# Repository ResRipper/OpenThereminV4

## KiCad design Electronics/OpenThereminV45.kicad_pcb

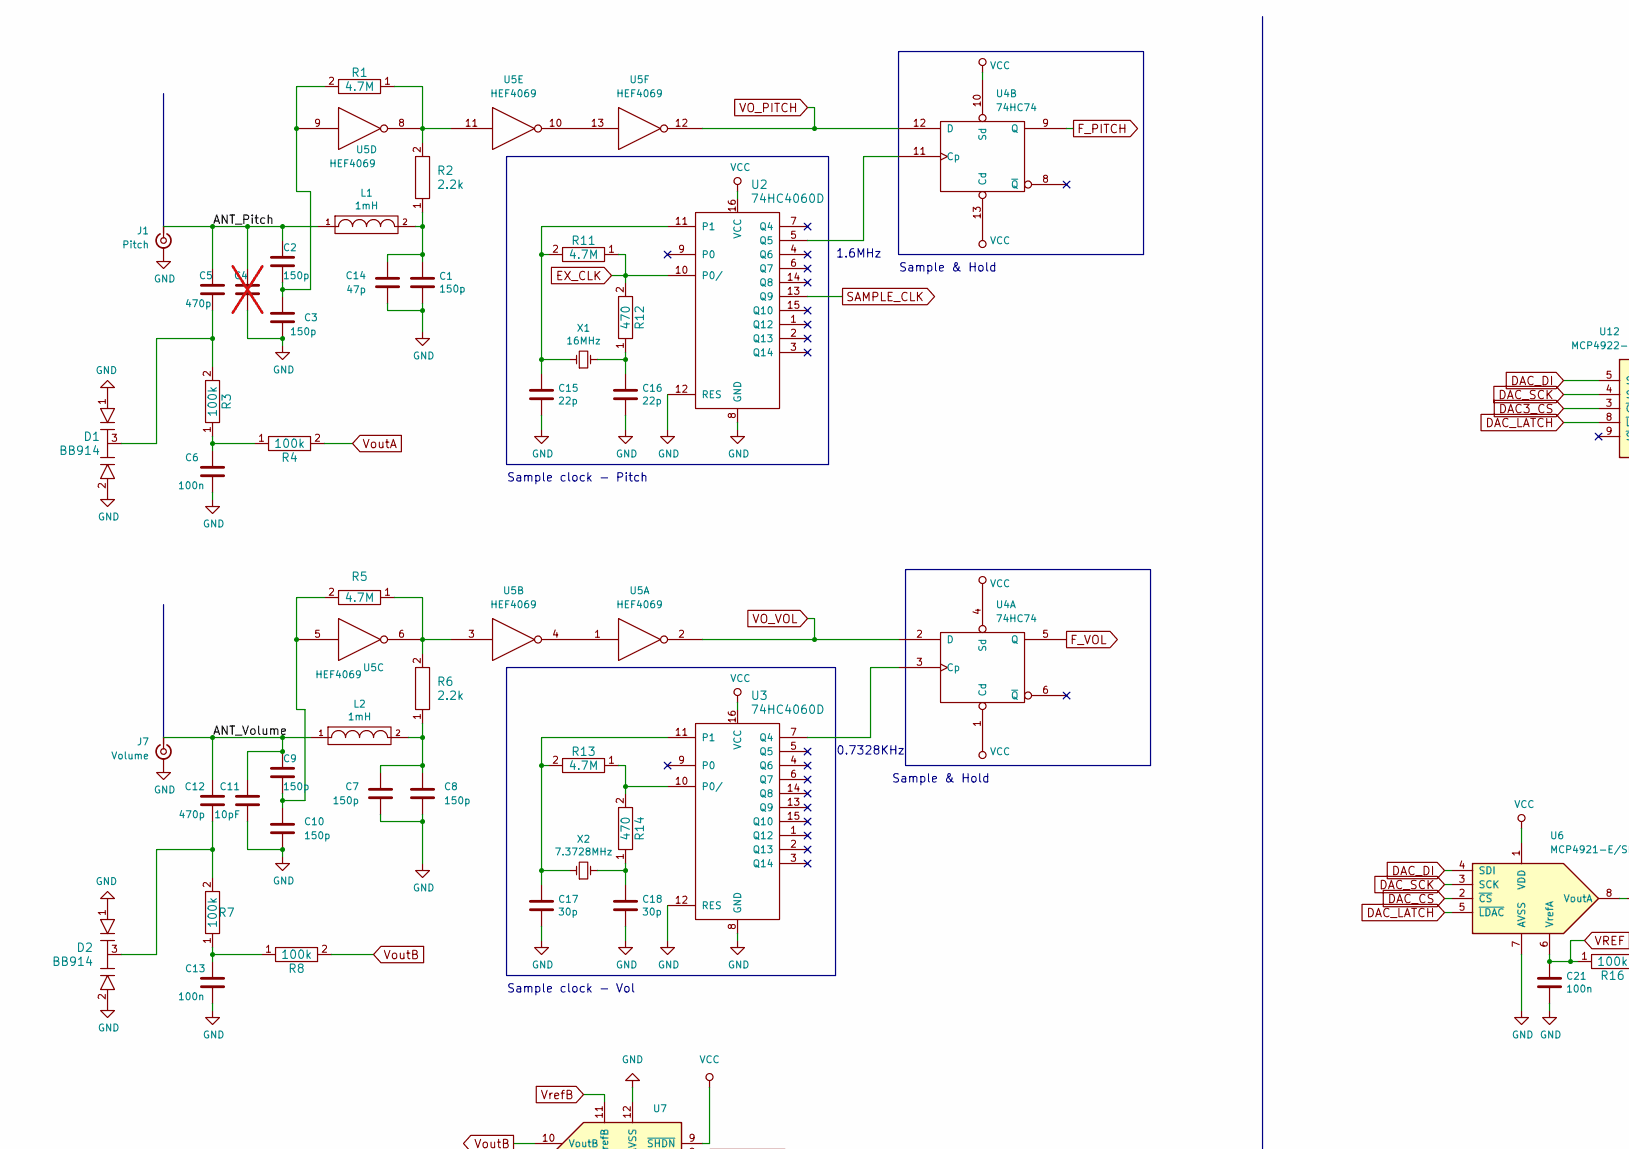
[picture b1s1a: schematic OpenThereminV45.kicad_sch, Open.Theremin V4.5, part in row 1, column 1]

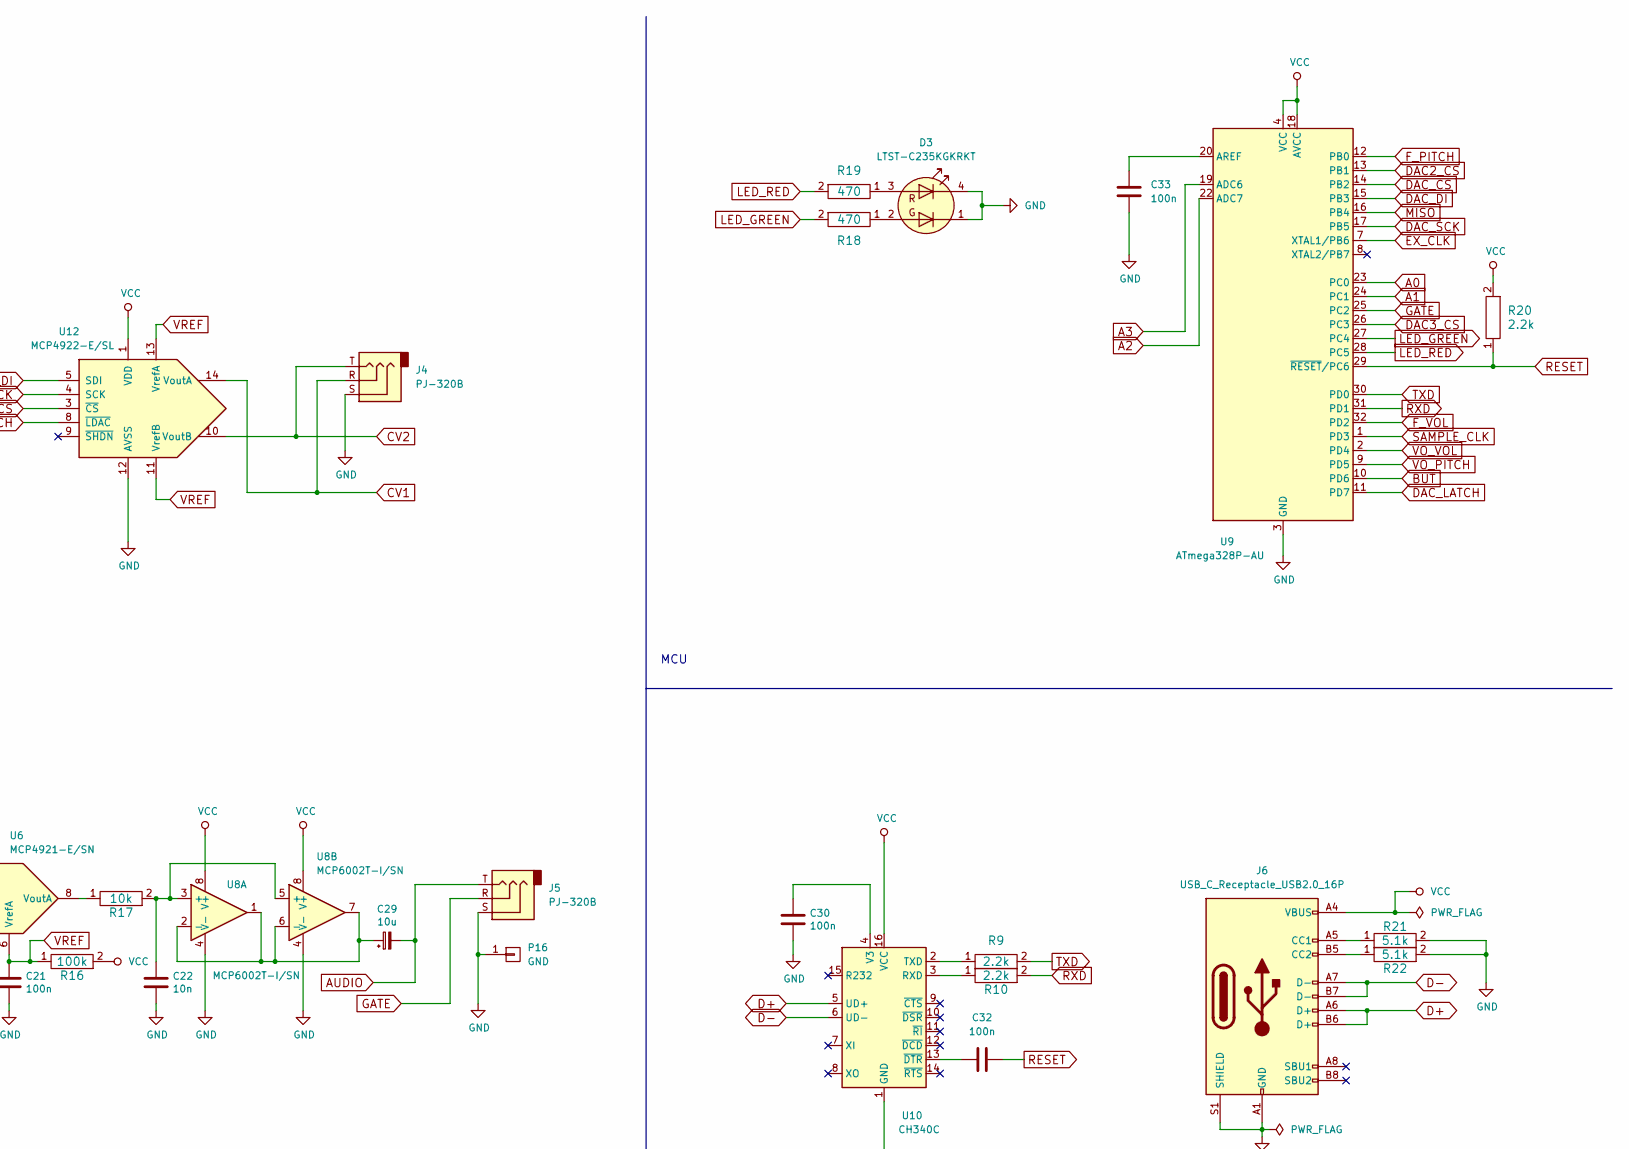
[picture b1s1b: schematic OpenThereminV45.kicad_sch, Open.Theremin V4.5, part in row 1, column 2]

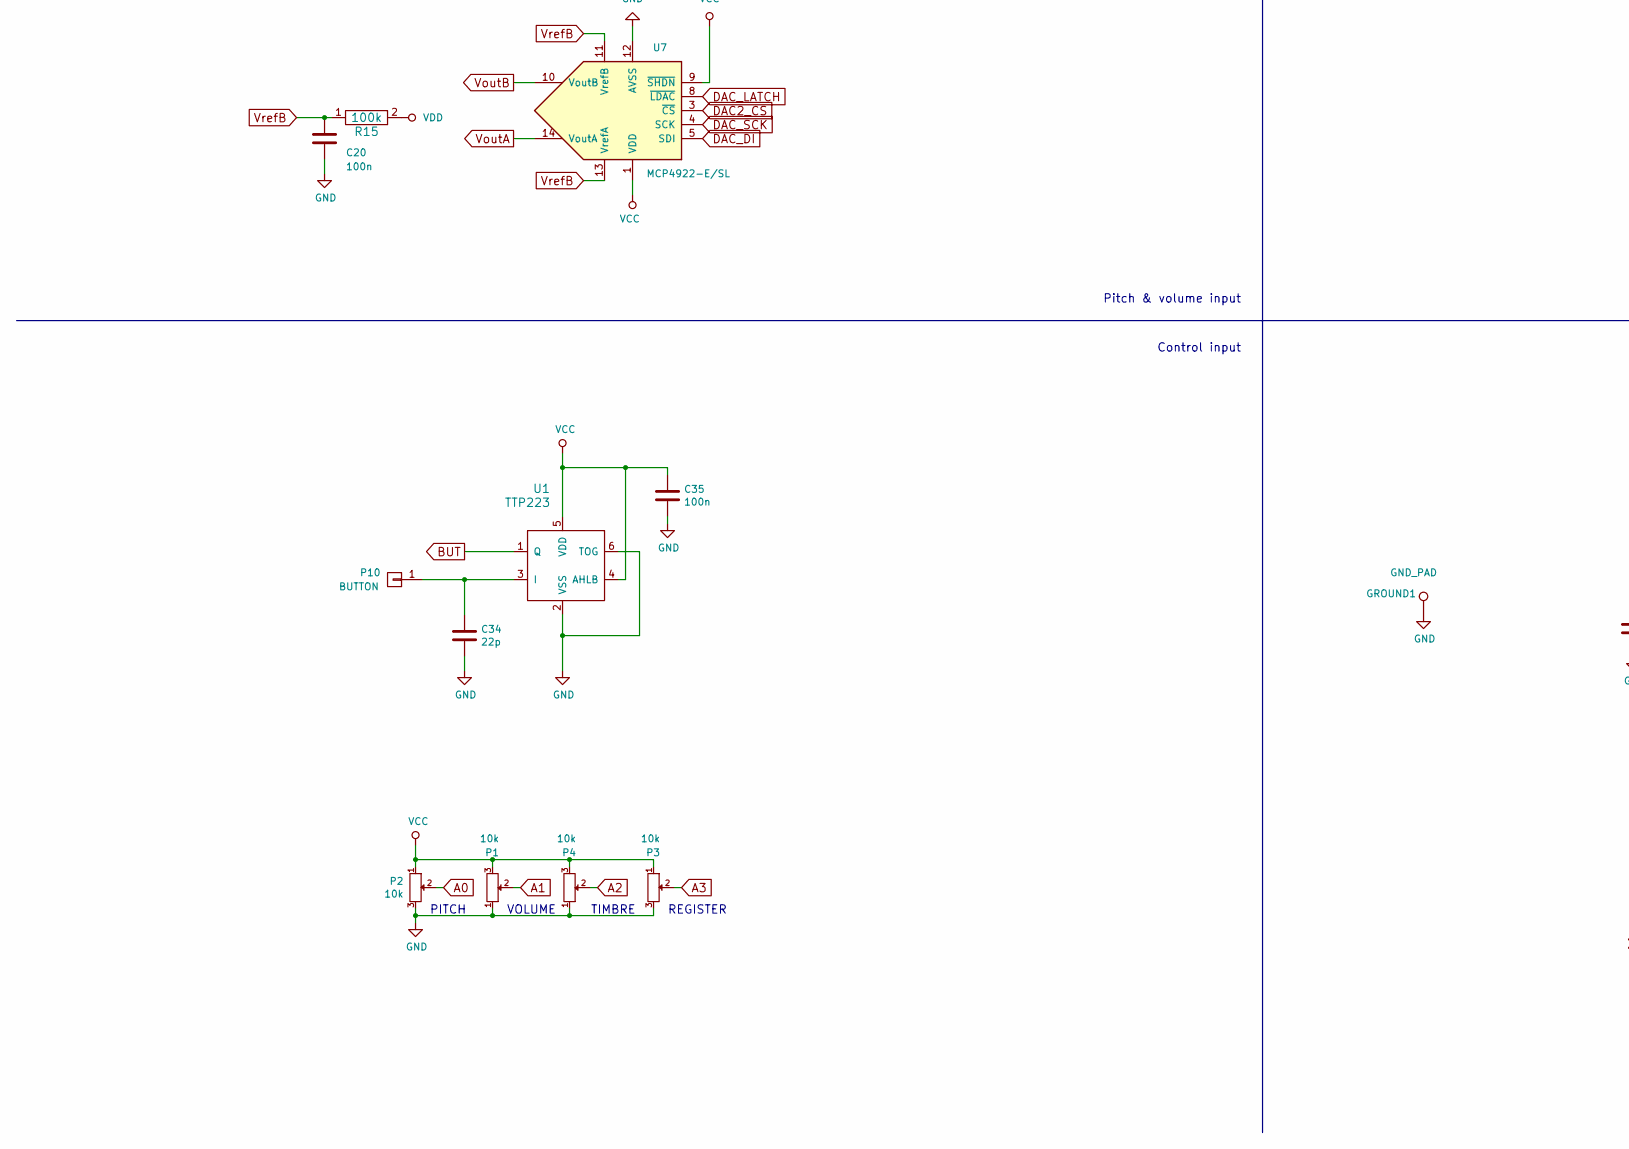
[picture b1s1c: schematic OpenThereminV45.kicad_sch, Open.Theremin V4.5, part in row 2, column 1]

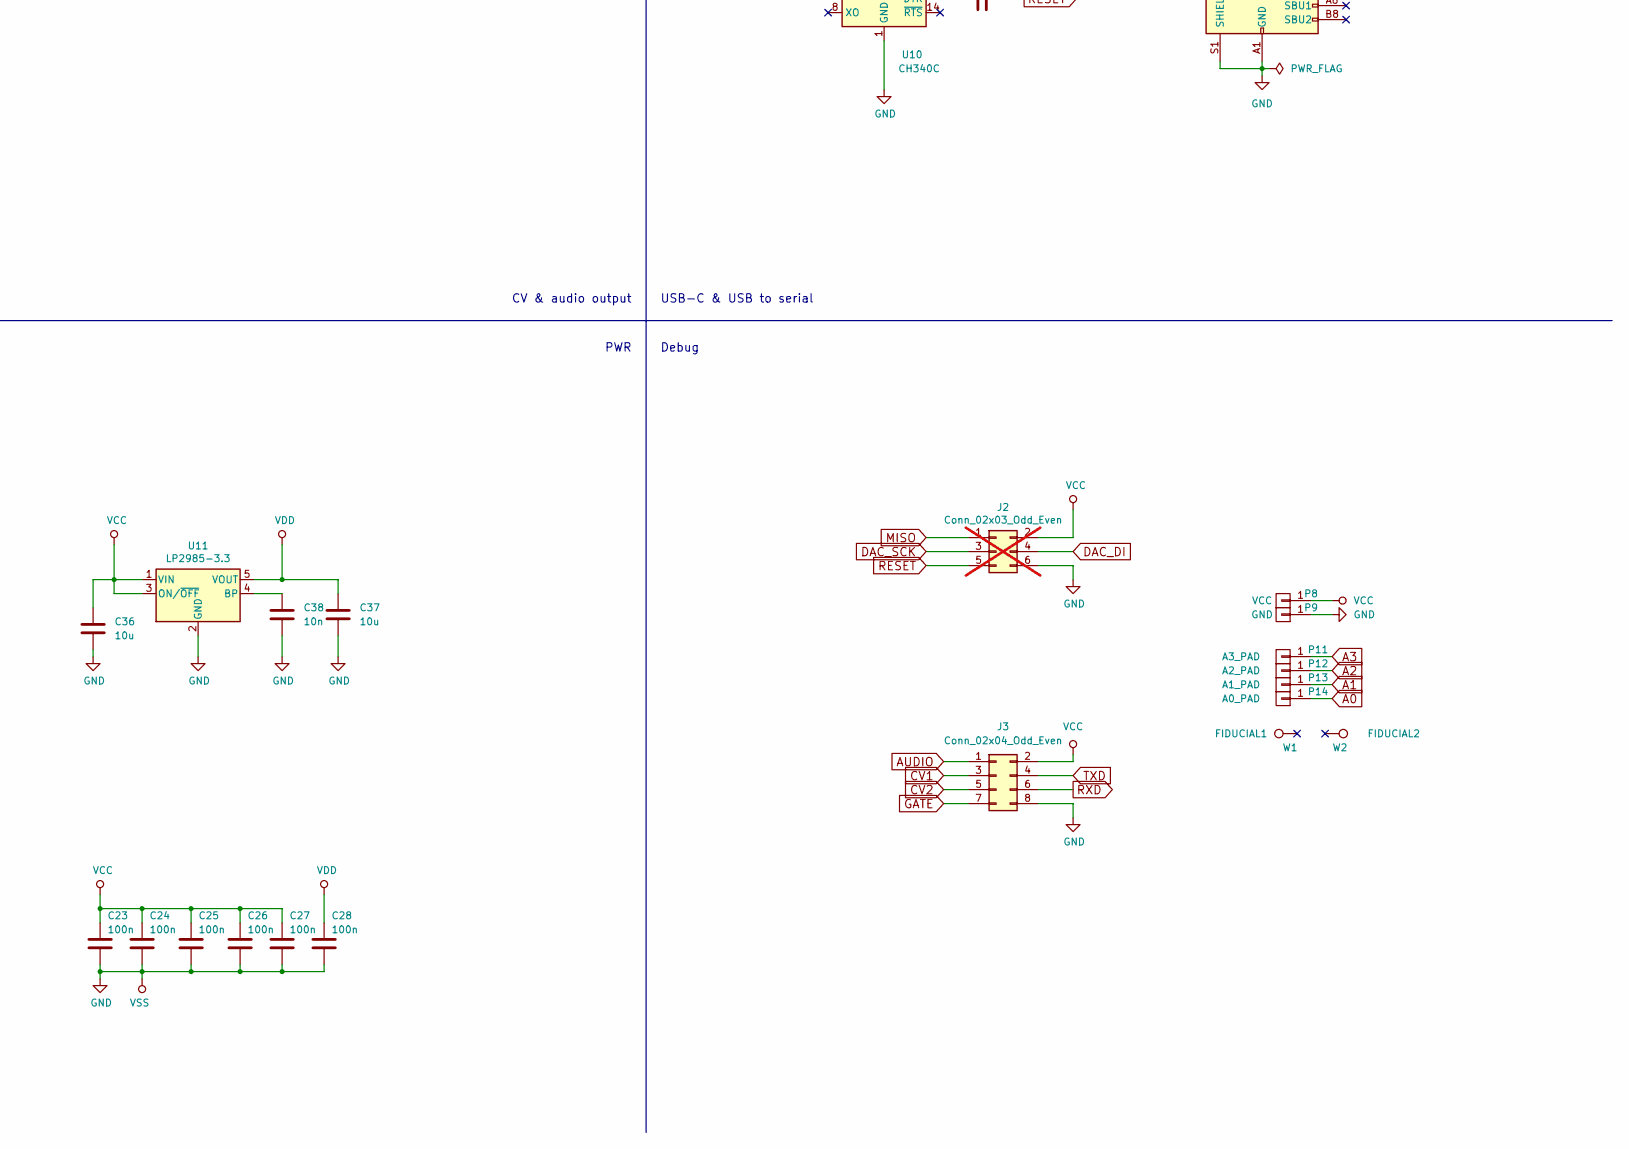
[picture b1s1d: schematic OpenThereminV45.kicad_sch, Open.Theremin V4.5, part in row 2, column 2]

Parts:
C1, C2, C3, C7, C8, C9, C10: 150p; C_0603_1608Metric; LCSC C107038
C4: C_0603_1608Metric; not fitted
C5, C12: 470p; C_0603_1608Metric; LCSC C106211
C6, C13, C20, C21, C23, C24, C25, C26, C27, C28, C30, C32, C33, C35: 100n; C_0603_1608Metric; LCSC C282519
C11: 10pF; C_0603_1608Metric; LCSC C376764
C14: 47p; C_0603_1608Metric; LCSC C94904
C15, C16, C34: 22p; C_0603_1608Metric; LCSC C105620
C17, C18: 30p; C_0603_1608Metric; LCSC C107047
C22, C38: 10n; C_0603_1608Metric; LCSC C376807
C29, C36, C37: 10u; C_0603_1608Metric; LCSC C1691
D1, D2: BB914; SOT-23; LCSC C3272485
D3: LTST-C235KGKRKT; LED_LiteOn_LTST-C235KGKRKT; LCSC C125110
GROUND1: GND_PAD; GNDPad
J1: Pitch; SMA_Amphenol_132134-11_Vertical; LCSC C5723187
J2: Conn_02x03_Odd_Even; Tag-Connect_TC2030-IDC-NL_2x03_P1.27mm_Vertical; not fitted
J3: Conn_02x04_Odd_Even; PinHeader_2x04_P1.27mm_Vertical_SMD; LCSC C19268845
J4, J5: PJ-320B; XKB_PJ-320B; LCSC C2884998
J6: USB_C_Receptacle_USB2.0_16P; USB_C_Receptacle_GCT_USB4105-xx-A_16P_TopMnt_Horizontal; LCSC C2988369
J7: Volume; SMA_Amphenol_132134-11_Vertical; LCSC C5723187
L1, L2: 1mH; L_1812_4532Metric; LCSC C394145
P1, P2, P3, P4: 10k; ALPS_RK09K1130A6S; LCSC C209770
P8: VCC; SMD_Pinheader_1_OT_BLANK
P9, P16: GND; SMD_Pinheader_1_OT_BLANK
P10: BUTTON; SensorButton
P11: A3_PAD; SMD_Pinheader_1_OT_BLANK
P12: A2_PAD; SMD_Pinheader_1_OT_BLANK
P13: A1_PAD; SMD_Pinheader_1_OT_BLANK
P14: A0_PAD; SMD_Pinheader_1_OT_BLANK
R1, R5, R11, R13: 4.7M; R_0603_1608Metric; LCSC C322165
R2, R6, R9, R10, R20: 2.2k; R_0603_1608Metric; LCSC C294652
R3, R4, R7, R8, R15, R16: 100k; R_0603_1608Metric; LCSC C3152121
R12, R14, R18, R19: 470; R_0603_1608Metric; LCSC C116694
R17: 10k; R_0603_1608Metric; LCSC C3152123
R21, R22: 5.1k; R_0603_1608Metric; LCSC C3152148
U1: TTP223; SOT-23-6; LCSC C5345654
U2, U3: 74HC4060D; SOIC-16_3.9x9.9mm_P1.27mm; LCSC C5649
U4: 74HC74; SOIC-14_3.9x8.7mm_P1.27mm; LCSC C27597
U5: HEF4069; SOIC-14_3.9x8.7mm_P1.27mm; LCSC C6739
U6: MCP4921-E/SN; SOIC-8_3.9x4.9mm_P1.27mm; LCSC C43499
U7, U12: MCP4922-E/SL; SOIC-14_3.9x8.7mm_P1.27mm; LCSC C39851
U8: MCP6002T-I/SN; SOIC-8_3.9x4.9mm_P1.27mm; LCSC C20538868
U9: ATmega328P-AU; TQFP-32_7x7mm_P0.8mm; LCSC C14877
U10: CH340C; SOIC-16_3.9x9.9mm_P1.27mm; LCSC C84681
U11: LP2985-3.3; SOT-23-5; LCSC C95414
W1: FIDUCIAL1; Fiducial_1mm_Dia_2.54mm_Outer_CopperBottom
W2: FIDUCIAL2; Fiducial_1mm_Dia_2.54mm_Outer_CopperBottom
X1: 16MHz; Crystal_SMD_HC49-SD; LCSC C7473031
X2: 7.3728MHz; Crystal_SMD_HC49-SD; LCSC C19173022

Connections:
/ANT_Pitch: C2.1, C4.1, C5.1, J1.1 (In), L1.1
/ANT_Volume: C9.1, C11.1, C12.1, J7.1 (In), L2.1
A0: P2.2, P14.1, U9.23 (PC0)
A1: P1.2, P13.1, U9.24 (PC1)
A2: P4.2, P12.1, U9.22 (ADC7)
A3: P3.2, P11.1, U9.19 (ADC6)
AUDIO: C29.2, J3.1, J5.T
BUT: U1.1 (Q), U9.10 (PD6)
CV1: J3.3, J4.R, U12.14 (VoutA)
CV2: J3.5, J4.T, U12.10 (VoutB)
D+: J6.A6 (D+), J6.B6 (D+), U10.5 (UD+)
D-: J6.A7 (D-), J6.B7 (D-), U10.6 (UD-)
DAC2_CS: U7.3 (~CS), U9.13 (PB1)
DAC3_CS: U9.26 (PC3), U12.3 (~CS)
DAC_CS: U6.2 (~CS), U9.14 (PB2)
DAC_DI: J2.4, U6.4 (SDI), U7.5 (SDI), U9.15 (PB3), U12.5 (SDI)
DAC_LATCH: U6.5 (~LDAC), U7.8 (~LDAC), U9.11 (PD7), U12.8 (~LDAC)
DAC_SCK: J2.3, U6.3 (SCK), U7.4 (SCK), U9.17 (PB5), U12.4 (SCK)
EX_CLK: R11.1, R12.2, U2.10 (P0/), U9.7 (XTAL1/PB6)
F_PITCH: U4.9 (Q), U9.12 (PB0)
F_VOL: U4.5 (Q), U9.32 (PD2)
GATE: J3.7, J5.R, U9.25 (PC2)
GND: C1.2, C3.2, C4.2, C6.2, C7.2, C8.2, C10.2, C11.2, C13.2, C14.2, C15.2, C16.2, C17.2, C18.2, C20.2, C21.2, C22.2, C23.2, C24.2, C25.2, C26.2, C27.2, C28.2, C30.2, C33.2, C34.2, C35.2, C36.2, C37.2, C38.2, D1.1, D1.2, D2.1, D2.2, D3.1 (K2), D3.4 (K1), GROUND1.1, J1.2 (Ext), J2.6, J3.8, J4.S, J5.S, J6.A1 (GND), J6.A12 (GND), J6.B1 (GND), J6.B12 (GND), J6.S1 (SHIELD), J7.2 (Ext), P1.1, P2.3, P3.3, P4.1, P9.1, P16.1, R21.2, R22.2, U1.2 (VSS), U1.6 (TOG), U2.8 (GND), U2.12 (RES), U3.8 (GND), U3.12 (RES), U4.7 (GND), U5.7 (VSS), U6.7 (AVSS), U7.12 (AVSS), U8.4 (V-), U9.3 (GND), U9.5 (GND), U9.21 (GND), U10.1 (GND), U11.2 (GND), U12.12 (AVSS)
LED_GREEN: R18.2, U9.27 (PC4)
LED_RED: R19.2, U9.28 (PC5)
MISO: J2.1, U9.16 (PB4)
unnamed: C1.1, C14.1, L1.2, R2.1
unnamed: C2.2, C3.1, R1.2, U5.9
unnamed: C5.2, D1.3, R3.2
unnamed: C6.1, R3.1, R4.1
unnamed: C7.1, C8.1, L2.2, R6.1
unnamed: C9.2, C10.1, R5.2, U5.5
unnamed: C12.2, D2.3, R7.2
unnamed: C13.1, R7.1, R8.1
unnamed: C16.1, R12.1, X1.2
unnamed: C18.1, R14.1, X2.2
unnamed: D3.3 (A1), R19.1
unnamed: D3.2 (A2), R18.1
unnamed: J6.A5 (CC1), R21.1
unnamed: J6.B5 (CC2), R22.1
unnamed: C34.1, P10.1, U1.3 (I)
unnamed: R1.1, R2.2, U5.8, U5.11
unnamed: R5.1, R6.2, U5.3, U5.6
unnamed: C15.1, R11.2, U2.11 (P1), X1.1
unnamed: U2.5 (Q5), U4.11 (Cp)
unnamed: R13.1, R14.2, U3.10 (P0/)
unnamed: C17.1, R13.2, U3.11 (P1), X2.1
unnamed: U3.7 (Q4), U4.3 (Cp)
unnamed: U5.1, U5.4
unnamed: U5.10, U5.13
unnamed: R17.1, U6.8 (VoutA)
unnamed: C22.1, R17.2, U8.3 (+), U8.5 (+)
unnamed: C29.1, U8.1, U8.2 (-), U8.6 (-), U8.7
unnamed: C33.1, U9.20 (AREF)
unnamed: R10.1, U10.3 (RXD)
unnamed: R9.1, U10.2 (TXD)
unnamed: C30.1, U10.4 (V3)
unnamed: C32.2, U10.13 (~DTR)
unnamed: C38.1, U11.4 (BP)
RESET: C32.1, J2.5, R20.1, U9.29 (~RESET/PC6)
RXD: J3.6, R10.2, U9.31 (PD1)
SAMPLE_CLK: U2.13 (Q9), U9.1 (PD3)
TXD: J3.4, R9.2, U9.30 (PD0)
VCC: C23.1, C24.1, C25.1, C26.1, C27.1, C35.1, C36.1, J2.2, J3.2, J6.A4 (VBUS), J6.A9 (VBUS), J6.B4 (VBUS), J6.B9 (VBUS), P1.3, P2.1, P3.1, P4.3, P8.1, R16.2, R20.2, U1.4 (AHLB), U1.5 (VDD), U2.16 (VCC), U3.16 (VCC), U4.1 (Cd), U4.4 (Sd), U4.10 (Sd), U4.13 (Cd), U4.14 (VCC), U6.1 (VDD), U7.1 (VDD), U7.9 (~SHDN), U8.8 (V+), U9.4 (VCC), U9.6 (VCC), U9.18 (AVCC), U10.16 (VCC), U11.1 (VIN), U11.3 (ON/~OFF), U12.1 (VDD)
VDD: C28.1, C37.1, R15.2, U5.14 (VDD), U11.5 (VOUT)
VO_PITCH: U4.12 (D), U5.12, U9.9 (PD5)
VO_VOL: U4.2 (D), U5.2, U9.2 (PD4)
VREF: C21.1, R16.1, U6.6 (VrefA), U12.11 (VrefB), U12.13 (VrefA)
VoutA: R4.2, U7.14 (VoutA)
VoutB: R8.2, U7.10 (VoutB)
VrefB: C20.1, R15.1, U7.11 (VrefB), U7.13 (VrefA)

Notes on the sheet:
Sample clock - Pitch
PWR
Sample & Hold
REGISTER
MCU
0.7328KHz
VOLUME
Pitch & volume input
TIMBRE
PITCH
Debug
USB-C & USB to serial
Sample clock - Vol
1.6MHz
CV & audio output
Control input

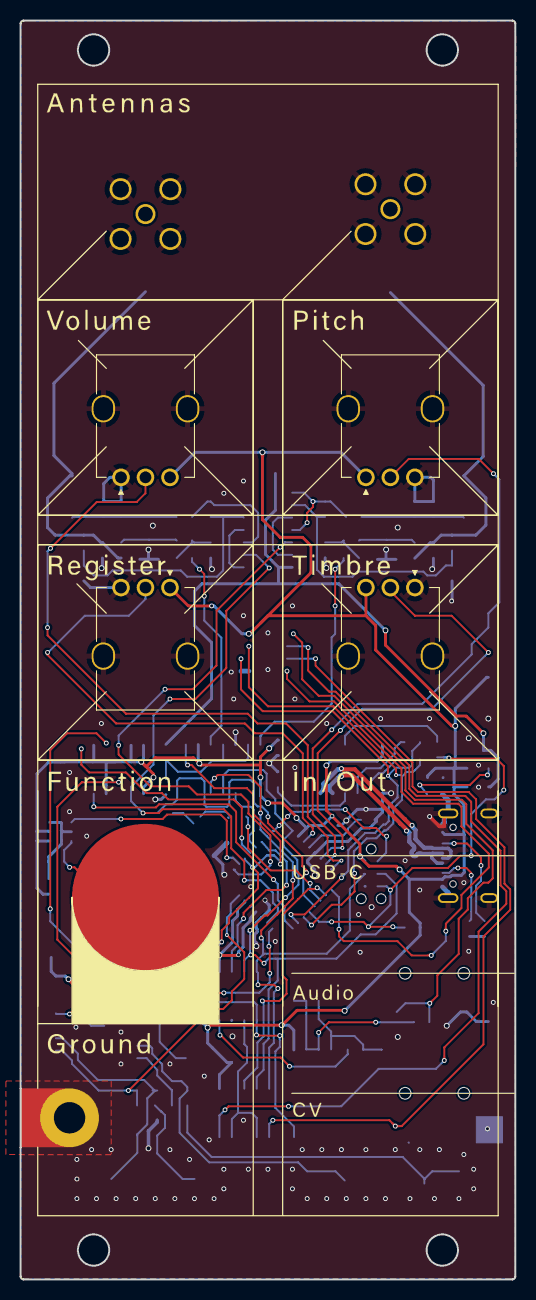
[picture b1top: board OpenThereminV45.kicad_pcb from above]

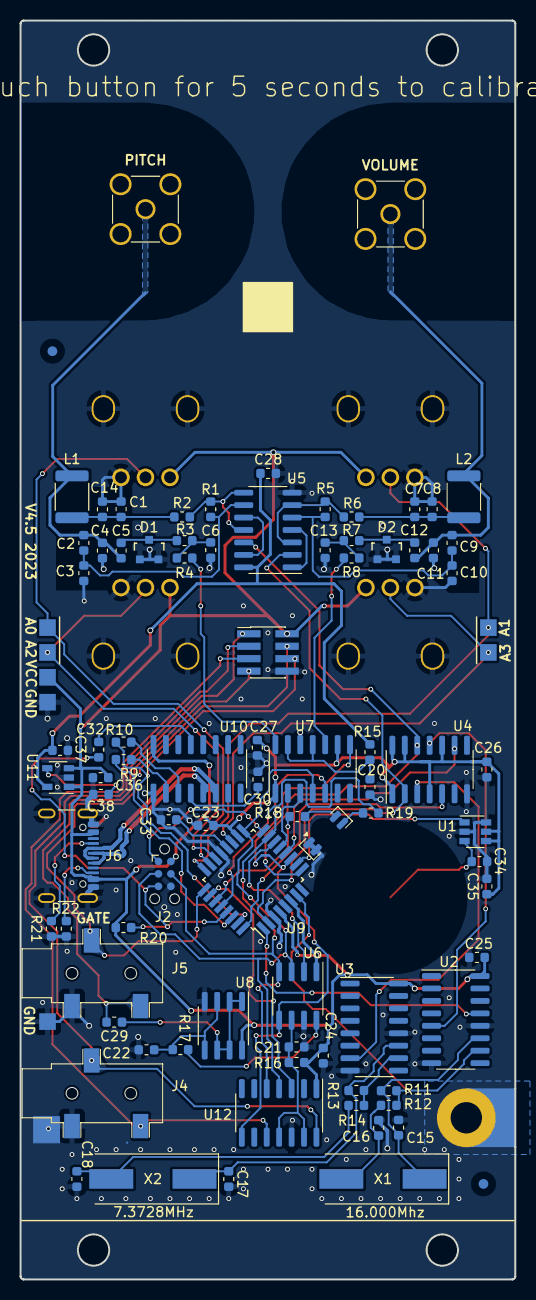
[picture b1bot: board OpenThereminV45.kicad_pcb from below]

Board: 2 copper layers, 50.5 x 128.5 mm, 99 parts (93 on the bottom side), 71 nets.

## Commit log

2024-09-24 Add JLC DRU file
2024-09-24 Update schema
    - Re-organize schema layout
    - Move DNP info from text description to part attribute
    - Move PN info from text description to part attribute
    - Fix I/O attribute for some pins and labels
    - Add NC labels for unused pins
    - Added LCSC, Vendor and PN info for most parts
2024-09-25 Remove outdated files
2024-09-25 Create library for project
2024-09-25 Update sym-lib-table
2024-09-25 Update schema & layout
    - Adjust layout base on JLC capabilities
    - Re-do USB layout
    - Replace 3.5mm jack, inductor, type-c connector and LED with higher availability option
    - Add 5x5mm SN block
    - Remove some logos and text for personal preference
2024-09-25 Generate wrl 3D model
2024-09-25 Generate gerber files
2024-09-25 Remove tag-connect from BOM
2024-09-25 Replace 02x05 pin connector with 02x04
2024-09-25 Update model base on recent change
2024-09-25 Set component info for ANT connector
2024-10-01 Update schema & layout
    - Use SMA as antenna connector
    - Replace potentiometers with cheaper & higher avaliability option
    - Re-route some of the traces
2024-10-01 Add Freecad
2024-10-01 Add BOM file
2024-10-01 Remove unneeded files
2024-10-02 Clean-up
2024-10-10 Minor changes to the layout
2024-10-14 Correct 2x4 pin header part info
